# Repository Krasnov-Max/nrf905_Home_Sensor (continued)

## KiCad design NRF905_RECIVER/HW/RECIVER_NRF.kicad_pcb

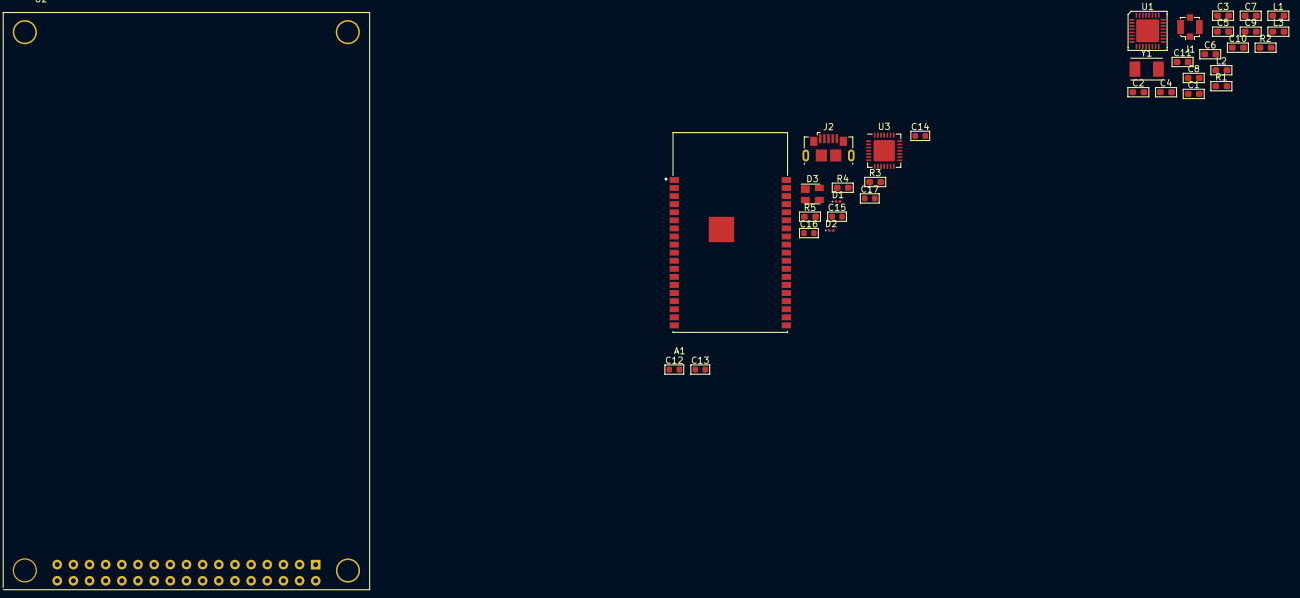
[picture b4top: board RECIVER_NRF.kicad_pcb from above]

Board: 2 copper layers, 35 parts (0 on the bottom side), 24 nets, no tracks yet.

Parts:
A1: ESP32-WROVER-I; ESP32-WROVER-IB
C1: 4.7 n; C_0603_1608Metric_Pad1.05x0.95mm_HandSolder
C2, C3: 22 p; C_0603_1608Metric_Pad1.05x0.95mm_HandSolder
C4: 10 n; C_0603_1608Metric_Pad1.05x0.95mm_HandSolder
C5, C6: 33 p; C_0603_1608Metric_Pad1.05x0.95mm_HandSolder
C7, C8: 18 p; C_0603_1608Metric_Pad1.05x0.95mm_HandSolder
C9: 6.8 p; C_0603_1608Metric_Pad1.05x0.95mm_HandSolder
C10: 180 p; C_0603_1608Metric_Pad1.05x0.95mm_HandSolder
C11: 3.3 n; C_0603_1608Metric_Pad1.05x0.95mm_HandSolder
C12, C13, C14, C15, C16, C17: C; C_0603_1608Metric
D1, D2: LED; LED_0201_0603Metric
D3: SP0503BAHT; SOT-143
J1: Conn_Coaxial; U.FL_Molex_MCRF_73412-0110_Vertical
J2: USB_B_Micro; USB_Micro-B_GCT_USB3076-30-A
L1: 12 n; L_0603_1608Metric_Pad1.05x0.95mm_HandSolder
L2, L3: 39 n; L_0603_1608Metric_Pad1.05x0.95mm_HandSolder
R1: 22 k; R_0603_1608Metric_Pad1.05x0.95mm_HandSolder
R2: 1 M; R_0603_1608Metric_Pad1.05x0.95mm_HandSolder
R3, R4, R5: R; R_0603_1608Metric_Pad1.05x0.95mm_HandSolder
U1: NRF905; QFN-32-1EP_5x5mm_P0.5mm_EP3.6x3.6mm
U2: 3.2_ILI9341_16bit; LCD_3.2_ILI9341
U3: CP2102N-A01-GQFN28; QFN-28-1EP_5x5mm_P0.5mm_EP3.35x3.35mm
Y1: Crystal; Crystal_SMD_TXC_7A-2Pin_5x3.2mm

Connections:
+3V3: C12.2, C13.2, U2.24, U2.25
/ESP32/VDD_ESP32: A1.2, C14.1, C15.1, C16.2, C17.2, R3.2, R4.2, R5.1, U3.6, U3.7
/NRF905/VDD_NRF: C1.2, C5.2, C6.2, U1.4, U1.17, U1.25
GND: C1.1, C2.2, C3.2, C4.2, C5.1, C6.1, C7.1, C8.1, C10.1, C11.2, J1.2, R1.2, U1.5, U1.9, U1.16, U1.18, U1.22, U1.24, U1.26, U1.27, U1.28, U1.29, U1.30
GNDREF: A1.1, A1.15, A1.38, C12.1, C13.1, C14.2, C15.2, C16.1, C17.1, D3.1, J2.5, J2.6, U2.26, U2.27, U2.35, U2.36, U2.37, U2.38, U3.3, U3.29
unnamed: A1.34, U3.26
unnamed: A1.35, U3.25
unnamed: C2.1, R2.1, U1.15, Y1.1
unnamed: C3.1, R2.2, U1.14, Y1.2
unnamed: C4.1, U1.31
unnamed: C7.2, L1.1, L2.1, U1.21
unnamed: C8.2, L1.2, L3.2, U1.20
unnamed: C9.1, J1.1
unnamed: C9.2, L2.2
unnamed: C10.2, C11.1, L3.1, U1.19
unnamed: D1.1, U3.19
unnamed: D1.2, R3.1
unnamed: D2.1, U3.18
unnamed: D2.2, R4.1
unnamed: D3.2, J2.1, U3.8
unnamed: D3.3, J2.3, U3.4
unnamed: D3.4, J2.2, U3.5
unnamed: R1.1, U1.23
unnamed: R5.2, U3.9

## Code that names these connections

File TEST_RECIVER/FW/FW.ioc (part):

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Mcu.Name=STM32F051R8Tx
Mcu.Package=LQFP64
Mcu.UserName=STM32F051R8Tx
PA13.Mode=Serial_Wire
PA13.Signal=SYS_SWDIO
PA14.Mode=Serial_Wire
PA14.Signal=SYS_SWCLK
PA3.GPIOParameters=GPIO_Label
PA3.GPIO_Label=LCD_LED
PA3.Signal=GPIO_Output
PA4.GPIOParameters=GPIO_Label
PA4.GPIO_Label=LCD_CS
PA4.Signal=GPIO_Output
PA5.GPIOParameters=GPIO_Label
PA5.GPIO_Label=LCD_CLK
PA5.Mode=Full_Duplex_Master
PA5.Signal=SPI1_SCK
PA6.GPIOParameters=GPIO_Label
PA6.GPIO_Label=LCD_MISO
PA6.Mode=Full_Duplex_Master
PA6.Signal=SPI1_MISO
PA7.GPIOParameters=GPIO_Label
PA7.GPIO_Label=LCD_MOSI
PA7.Mode=Full_Duplex_Master
PA7.Signal=SPI1_MOSI
PA8.GPIOParameters=GPIO_Label
PA8.GPIO_Label=NRF_AM
PA8.Signal=GPIO_Input
PA9.GPIOParameters=GPIO_Label
PA9.GPIO_Label=NRF_CD
PA9.Signal=GPIO_Input
PB12.GPIOParameters=GPIO_Label
PB12.GPIO_Label=NRF_CS
PB12.Signal=GPIO_Output
PB13.GPIOParameters=GPIO_Label
PB13.GPIO_Label=NRF_CLK
PB13.Mode=Full_Duplex_Master
PB13.Signal=SPI2_SCK
PB14.GPIOParameters=GPIO_Label
PB14.GPIO_Label=NRF_MISO
PB14.Mode=Full_Duplex_Master
PB14.Signal=SPI2_MISO
PB15.GPIOParameters=GPIO_Label
PB15.GPIO_Label=NRF_MOSI
PB15.Mode=Full_Duplex_Master
PB15.Signal=SPI2_MOSI
PC6.GPIOParameters=GPIO_Label
PC6.GPIO_Label=NRF_PWR
PC6.Signal=GPIO_Output
PC7.GPIOParameters=GPIO_Label
PC7.GPIO_Label=NRF_CE
PC7.Signal=GPIO_Output
PC8.GPIOParameters=GPIO_Label
PC8.GPIO_Label=NRF_TXEN
PC8.Signal=GPIO_Output
PC9.GPIOParameters=GPIO_Label
PC9.GPIO_Label=NRF_DR
PC9.Signal=GPXTI9
PF0-OSC_IN.Mode=HSE-External-Oscillator
PF0-OSC_IN.Signal=RCC_OSC_IN
PF1-OSC_OUT.Mode=HSE-External-Oscillator
PF1-OSC_OUT.Signal=RCC_OSC_OUT
PF4.GPIOParameters=GPIO_Label
PF4.GPIO_Label=LCD_DC
PF4.Signal=GPIO_Output
PF5.GPIOParameters=GPIO_Label
PF5.GPIO_Label=LCD_RES
PF5.Signal=GPIO_Output
RCC.SYSCLKFreq_VALUE=48000000
RCC.SYSCLKSource=RCC_SYSCLKSOURCE_PLLCLK
board=custom

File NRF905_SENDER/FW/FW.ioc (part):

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Mcu.Name=STM32L051C(6-8)Tx
Mcu.Package=LQFP48
Mcu.UserName=STM32L051C6Tx
PA0.Mode=IN0
PA0.Signal=ADC_IN0
PA1.GPIOParameters=GPIO_Label
PA1.GPIO_Label=TRX_CE
PA1.Signal=GPIO_Output
PA10.GPIOParameters=GPIO_Label
PA10.GPIO_Label=StepUP_EN
PA10.Signal=GPIO_Output
PA11.GPIOParameters=GPIO_Label
PA11.GPIO_Label=SlaveDevice
PA11.Signal=GPIO_Output
PA12.GPIOParameters=GPIO_Label
PA12.GPIO_Label=KEY
PA12.Signal=GPIO_Input
PA13.Mode=Serial_Wire
PA13.Signal=SYS_SWDIO
PA14.Mode=Serial_Wire
PA14.Signal=SYS_SWCLK
PA15.GPIOParameters=GPIO_Label
PA15.GPIO_Label=NRF_POWER
PA15.Signal=GPIO_Output
PA2.GPIOParameters=GPIO_Label
PA2.GPIO_Label=TX_EN
PA2.Signal=GPIO_Output
PA3.GPIOParameters=GPIO_Label
PA3.GPIO_Label=CS_BME
PA3.Signal=GPIO_Output
PA4.GPIOParameters=GPIO_Label
PA4.GPIO_Label=CS_NRF
PA4.Signal=GPIO_Output
PA5.Mode=Full_Duplex_Master
PA5.Signal=SPI1_SCK
PA6.Mode=Full_Duplex_Master
PA6.Signal=SPI1_MISO
PA7.Mode=Full_Duplex_Master
PA7.Signal=SPI1_MOSI
PA8.GPIOParameters=GPIO_Label
PA8.GPIO_Label=LED_1
PA8.Signal=GPIO_Output
PA9.GPIOParameters=GPIO_Label
PA9.GPIO_Label=LED_2
PA9.Signal=GPIO_Output
PB0.GPIOParameters=GPIO_Label
PB0.GPIO_Label=DR
PB0.Signal=GPXTI0
PB6.Mode=Asynchronous
PB6.Signal=USART1_TX
PB7.Mode=Asynchronous
PB7.Signal=USART1_RX
RCC.HSE_VALUE=8000000
RCC.SYSCLKFreq_VALUE=2097000
board=custom

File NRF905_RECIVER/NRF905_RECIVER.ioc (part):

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Mcu.Name=STM32F401R(D-E)Tx
Mcu.Package=LQFP64
Mcu.UserName=STM32F401RETx
PA13.GPIOParameters=GPIO_Label
PA13.GPIO_Label=TMS
PA13.Signal=SYS_JTMS-SWDIO
PA14.GPIOParameters=GPIO_Label
PA14.GPIO_Label=TCK
PA14.Signal=SYS_JTCK-SWCLK
PA2.GPIOParameters=GPIO_Speed,GPIO_PuPd,GPIO_Label,GPIO_Mode
PA2.GPIO_Label=USART_TX
PA2.GPIO_Mode=GPIO_MODE_AF_PP
PA2.GPIO_PuPd=GPIO_NOPULL
PA2.GPIO_Speed=GPIO_SPEED_FREQ_LOW
PA2.Mode=Asynchronous
PA2.Signal=USART2_TX
PA3.GPIOParameters=GPIO_Speed,GPIO_PuPd,GPIO_Label,GPIO_Mode
PA3.GPIO_Label=USART_RX
PA3.GPIO_Mode=GPIO_MODE_AF_PP
PA3.GPIO_PuPd=GPIO_NOPULL
PA3.GPIO_Speed=GPIO_SPEED_FREQ_LOW
PA3.Mode=Asynchronous
PA3.Signal=USART2_RX
PA5.GPIOParameters=GPIO_Speed,GPIO_PuPd,GPIO_Label,GPIO_Mode
PA5.GPIO_Label=LD2 [Green Led]
PA5.GPIO_Mode=GPIO_MODE_OUTPUT_PP
PA5.GPIO_PuPd=GPIO_NOPULL
PA5.GPIO_Speed=GPIO_SPEED_FREQ_LOW
PA5.Signal=GPIO_Output
PB13.GPIOParameters=GPIO_Label
PB13.GPIO_Label=CD
PB13.Signal=GPIO_Input
PB14.GPIOParameters=GPIO_Label
PB14.GPIO_Label=AM
PB14.Signal=GPIO_Input
PB15.GPIOParameters=GPIO_Label
PB15.GPIO_Label=DR
PB15.Signal=GPIO_Input
PB3.GPIOParameters=GPIO_Label
PB3.GPIO_Label=SWO
PB3.Signal=SYS_JTDO-SWO
PC10.Mode=Full_Duplex_Master
PC10.Signal=SPI3_SCK
PC11.Mode=Full_Duplex_Master
PC11.Signal=SPI3_MISO
PC12.Mode=Full_Duplex_Master
PC12.Signal=SPI3_MOSI
PC13-ANTI_TAMP.GPIOParameters=GPIO_PuPd,GPIO_Label,GPIO_ModeDefaultEXTI
PC13-ANTI_TAMP.GPIO_Label=B1 [Blue PushButton]
PC13-ANTI_TAMP.GPIO_ModeDefaultEXTI=GPIO_MODE_IT_FALLING
PC13-ANTI_TAMP.GPIO_PuPd=GPIO_NOPULL
PC13-ANTI_TAMP.Signal=GPXTI13
PC14-OSC32_IN.Signal=RCC_OSC32_IN
PC15-OSC32_OUT.Signal=RCC_OSC32_OUT
PC6.GPIOParameters=GPIO_Label
PC6.GPIO_Label=CE
PC6.Signal=GPIO_Output
PC7.GPIOParameters=GPIO_Label
PC7.GPIO_Label=TXE
PC7.Signal=GPIO_Output
PC8.GPIOParameters=GPIO_Label
PC8.GPIO_Label=PWR
PC8.Signal=GPIO_Output
PC9.GPIOParameters=GPIO_Label
PC9.GPIO_Label=CS_NRF
PC9.Signal=GPIO_Output
PH0\ -\ OSC_IN.Signal=RCC_OSC_IN
PH1\ -\ OSC_OUT.Signal=RCC_OSC_OUT
RCC.HSE_VALUE=8000000
RCC.SYSCLKFreq_VALUE=16000000
board=NUCLEO-F401RE
boardIOC=true

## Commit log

2020-09-19 Добавле шаблон схематика для приемника Оптимизирована и унифицирована стркутура каталогов для файлов проекта Добален шаблон прошивки приемника
2020-09-19 Изменение в схемотехнике приемника. Добавлен TFT модуль, WIFI модуль.
2020-10-10 Изменена структура проека. Добавлен шаблон проекта для ESP32. Изменение в схемотехнике WIFI модуль с ESP-07 изменени на ESP32 WROVER-IB
2020-10-10 Изменено имя проекта в ESP32
2020-10-11 Добавлена тестовая прошивка для Sender. Исправленны ошибки в печатной плате
2020-10-11 Удалены катологи с бинарниками сборки
2020-10-11 Удалены bak файлы и Gerber паты с ошибками
2021-02-10 Version 0.1 work
2021-02-12 Change MCU. New MCU STM32L051
2021-02-12 Change FW. Using LL over HAL. Change schematics for new MCU
2021-02-22 new scematics. New PCB.
2021-03-28 Change ESP32
